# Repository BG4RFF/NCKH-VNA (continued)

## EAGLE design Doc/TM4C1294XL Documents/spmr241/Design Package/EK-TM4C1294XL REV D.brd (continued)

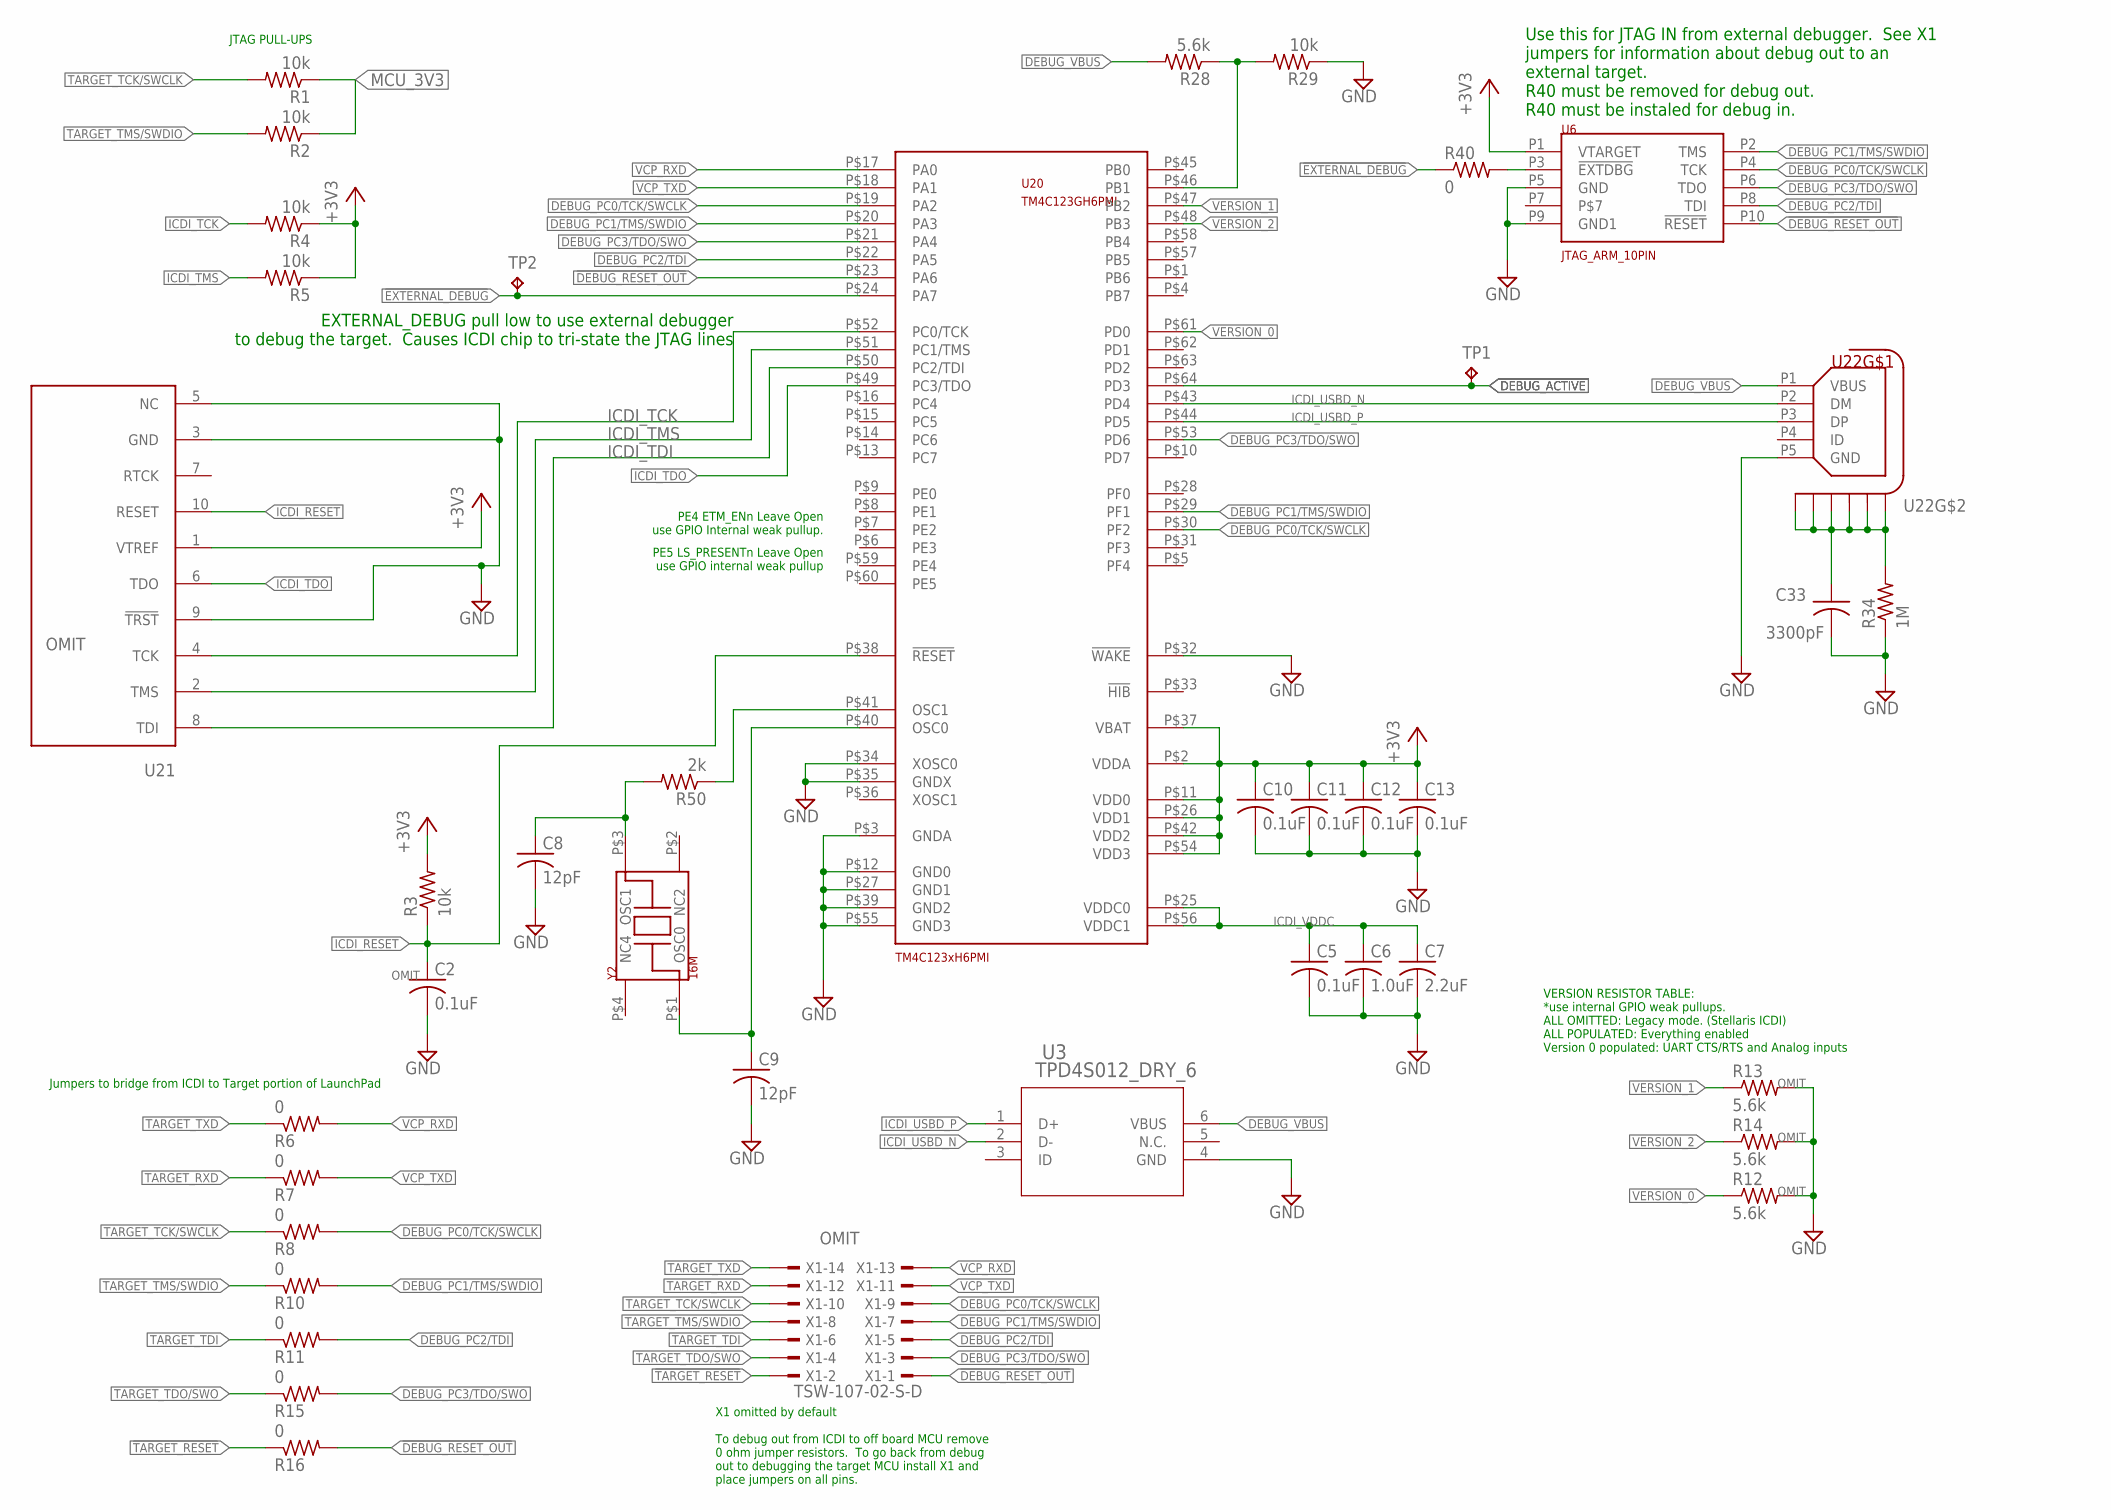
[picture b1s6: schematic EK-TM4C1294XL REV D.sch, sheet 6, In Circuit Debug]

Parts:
C2, C5, C10, C11, C12, C13: 0.1uF; C0402
C6: 1.0uF; C0402
C7: 2.2uF; C0603
C8, C9: 12pF; C0402
C33: 3300pF; C0603
R1, R2, R3, R4, R5, R29: 10k; R0402
R6, R7, R8, R10, R11, R15, R16, R40: 0; R0402
R12, R13, R14, R28: 5.6k; R0402
R34: 1M; R0603
R50: 2k; R0402
TP1, TP2: TPPAD1-13; P1-13
U3: TPD4S012_DRY_6; DRY6
U6: JTAG_ARM_10PIN; CON_2X5_50MIL
U20: TM4C123GH6PMI; LQFP-64-PM
U21: TC2050-NL-MCP-NL; TC2030-MCP-NL
U22: CON_USB_FCI_MICRO_B_10118194; CON_USB_MICRO_B_FCI_10118194
X1: TSW-107-02-S-D
Y2: 16M; NDK3.2X2.5

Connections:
!DEBUG_RESET_OUT: R16.2, U6.P10 (!RESET), U20.P$23 (PA6), X1.1
!EXTERNAL_DEBUG: R40.1, TP2.TP, U20.P$24 (PA7)
!TARGET_RESET: R16.1, X1.2; also elsewhere on the board
+3V3: C10.1, C11.1, C12.1, C13.1, R3.2, R4.1, R5.1, U6.P1 (VTARGET), U20.P$2 (VDDA), U20.P$11 (VDD0), U20.P$26 (VDD1), U20.P$37 (VBAT), U20.P$42 (VDD2), U20.P$54 (VDD3), U21.1 (VTREF); also elsewhere on the board
DEBUG_ACTIVE: TP1.TP, U20.P$64 (PD3)
DEBUG_PC0/TCK/SWCLK: R8.2, U6.P4 (TCK), U20.P$19 (PA2), U20.P$30 (PF2), X1.9
DEBUG_PC1/TMS/SWDIO: R10.2, U6.P2 (TMS), U20.P$20 (PA3), U20.P$29 (PF1), X1.7
DEBUG_PC2/TDI: R11.2, U6.P8 (TDI), U20.P$22 (PA5), X1.5
DEBUG_PC3/TDO/SWO: R15.2, U6.P6 (TDO), U20.P$21 (PA4), U20.P$53 (PD6), X1.3
DEBUG_VBUS: R28.2, U3.6 (VBUS), U22.P1 (VBUS); also elsewhere on the board
GND: C2.2, C5.2, C6.2, C7.2, C8.2, C9.2, C10.2, C11.2, C12.2, C13.2, C33.2, R12.2, R13.2, R14.2, R29.1, R34.1, U3.4 (GND), U6.P5 (GND), U6.P9 (GND1), U20.P$3 (GNDA), U20.P$12 (GND0), U20.P$27 (GND1), U20.P$32 (!WAKE), U20.P$34 (XOSC0), U20.P$35 (GNDX), U20.P$39 (GND2), U20.P$55 (GND3), U21.3 (GND), U21.5 (NC), U21.9 (!TRST), U22.P5 (GND); also elsewhere on the board
ICDI_RESET: C2.1, R3.1, U20.P$38 (!RESET), U21.10 (RESET)
ICDI_TCK: R4.2, U20.P$52 (PC0/TCK), U21.4 (TCK)
ICDI_TDI: U20.P$50 (PC2/TDI), U21.8 (TDI)
ICDI_TDO: U20.P$49 (PC3/TDO), U21.6 (TDO)
ICDI_TMS: R5.2, U20.P$51 (PC1/TMS), U21.2 (TMS)
ICDI_USBD_N: U3.2 (D-), U20.P$43 (PD4), U22.P2 (DM)
ICDI_USBD_P: U3.1 (D+), U20.P$44 (PD5), U22.P3 (DP)
ICDI_VDDC: C5.1, C6.1, C7.1, U20.P$25 (VDDC0), U20.P$56 (VDDC1)
MCU_3V3: R1.1, R2.1; also elsewhere on the board
unnamed: C9.1, U20.P$40 (OSC0), Y2.P$1 (OSC0)
unnamed: C8.1, R50.2, Y2.P$3 (OSC1)
unnamed: R40.2, U6.P3 (!EXTDBG)
unnamed: R28.1, R29.2, U20.P$46 (PB1)
unnamed: R50.1, U20.P$41 (OSC1)
unnamed: C33.1, R34.2, U22.P6 (S1), U22.P7 (S2), U22.P8 (S3), U22.P9 (S4), U22.P10 (S5), U22.P11 (S6)
TARGET_RXD: R7.1, X1.12; also elsewhere on the board
TARGET_TCK/SWCLK: R1.2, R8.1, X1.10; also elsewhere on the board
TARGET_TDI: R11.1, X1.6; also elsewhere on the board
TARGET_TDO/SWO: R15.1, X1.4; also elsewhere on the board
TARGET_TMS/SWDIO: R2.2, R10.1, X1.8; also elsewhere on the board
TARGET_TXD: R6.1, X1.14; also elsewhere on the board
VCP_RXD: R6.2, U20.P$17 (PA0), X1.13
VCP_TXD: R7.2, U20.P$18 (PA1), X1.11
VERSION_0: R12.1, U20.P$61 (PD0)
VERSION_1: R13.1, U20.P$47 (PB2)
VERSION_2: R14.1, U20.P$48 (PB3)

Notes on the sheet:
PE4 ETM_ENn Leave Open use GPIO Internal weak pullup.
PE5 LS_PRESENTn Leave Open use GPIO internal weak pullup
VERSION RESISTOR TABLE: *use internal GPIO weak pullups. ALL OMITTED: Legacy mode. (Stellaris ICDI) ALL POPULATED: Everything enabled Version 0 populated: UART CTS/RTS and Analog inputs
JTAG PULL-UPS
Jumpers to bridge from ICDI to Target portion of LaunchPad
EXTERNAL_DEBUG pull low to use external debugger to debug the target. Causes ICDI chip to tri-state the JTAG lines
Use this for JTAG IN from external debugger. See X1 jumpers for information about debug out to an external target. R40 must be removed for debug out. R40 must be instaled for debug in.
X1 omitted by default To debug out from ICDI to off board MCU remove 0 ohm jumper resistors. To go back from debug out to debugging the target MCU install X1 and place jumpers on all pins.

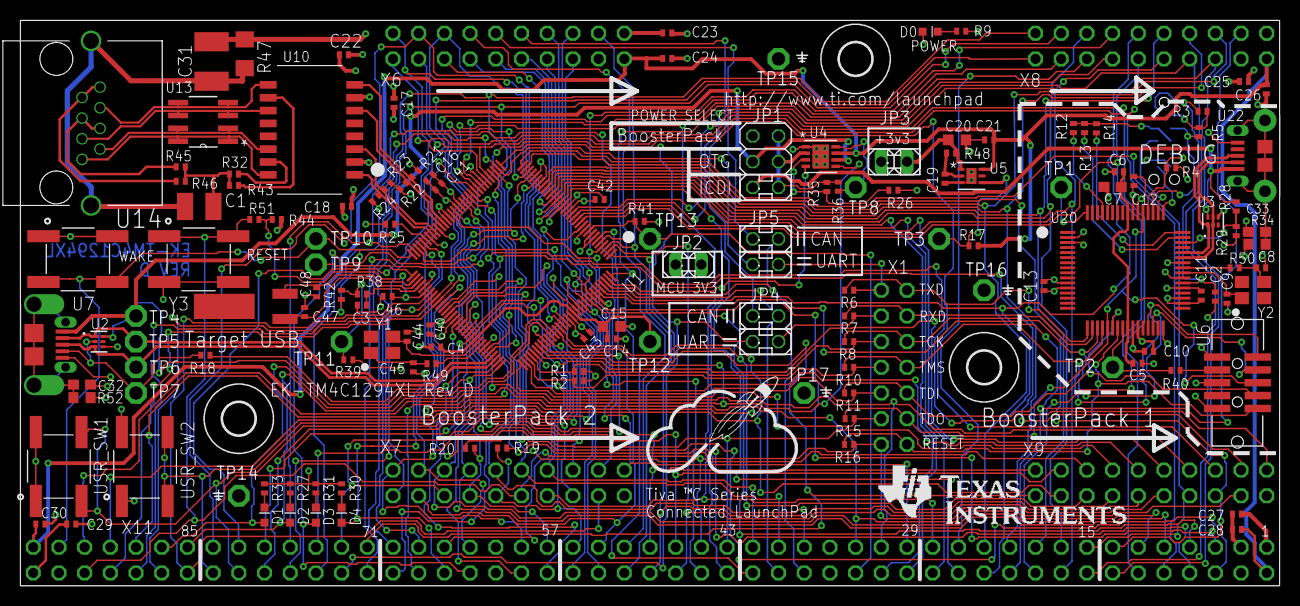
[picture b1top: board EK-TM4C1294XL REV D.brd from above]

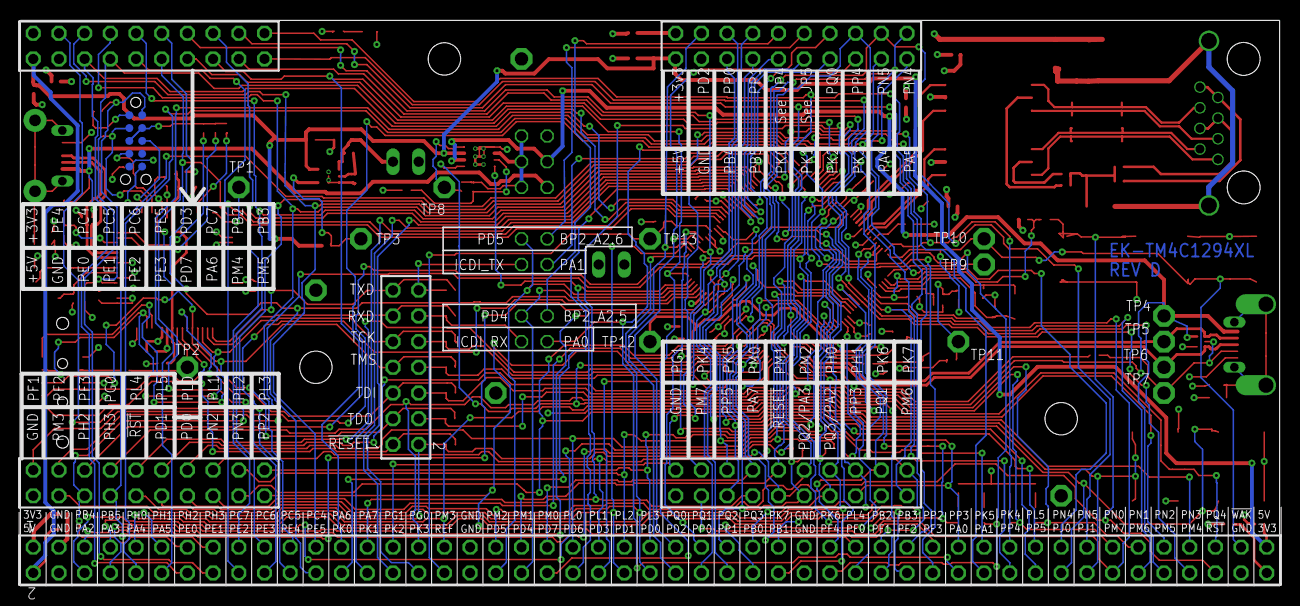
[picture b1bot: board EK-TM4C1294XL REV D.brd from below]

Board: 4 copper layers, 124.5 x 55.9 mm, 156 parts (7 on the bottom side), 166 nets.

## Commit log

2017-05-13 Add: Documents
2017-05-13 Add: VNA_Arduino ADC, GPIO, I2C drivers
2017-05-13 Add: VNA_Arduino SPI & UART Driver
2017-05-14 Add: VNA_Arduino AD8302, Button, HC-05; Update: GPIO, UART
2017-05-15 Add: LCD 5110 Library
2017-05-17 Add: ADF8302 freqency setting
2017-05-20 Add: STM32F103C8T6 document and sample projects
2017-05-20 Add: VNA_STM32F103C8T6 project and Button_Control library for STM32F103C8T6
2017-05-26 Add: VNA_STM32F103C8T6 ADC & SPI
2017-05-28 Add: Proteus demo board sch & pcb; Update: VNA_STM32F103C8T6 code on demo board, simple menu
2017-06-18 Add: iMindMap file
2017-07-23 Add: cJSON library and test for Arduino & STM32F103C8T6 (both failed)
2017-07-25 Add: Task excel file; Update: DemoBoard2 Schematic with ADF_Control header
2017-07-30 Add: VNA_TM4C1294XL project (include Button, UART & ADC modules, but not tested) + Arduino sketch used for controlling black ADF board, technically worked with wrong frequencies (~2GHz-3.8GHz)
2017-08-08 Update: VNA_STM32F103C8T6 ADC_Driver read mag & phs methods return float value.
2017-08-08 Update: VNA_TM4C1294XL
2017-08-12 Update: VNA_TM4C1294XL add ScreenManager and Screen
2017-08-12 Update: VNA_TM4C1294XL update all delay by SysTick
2017-08-19 VNA_TM4c1294XL tested UART, SPI, ADC complete ok
2017-08-30 VNA_TM4C1294XL ALL DRIVERS OK
2018-03-17 Update: Add bao cao cuoi ky NCKH
2018-03-17 Update: Them bao cao tong ket & bao cao tai chinh
2018-03-18 Update: Chinh sua bao cao cuoi ky
2018-03-18 Update: Xoa file bao cao tong ket nhap
2018-03-22 Update: Bao cao final
